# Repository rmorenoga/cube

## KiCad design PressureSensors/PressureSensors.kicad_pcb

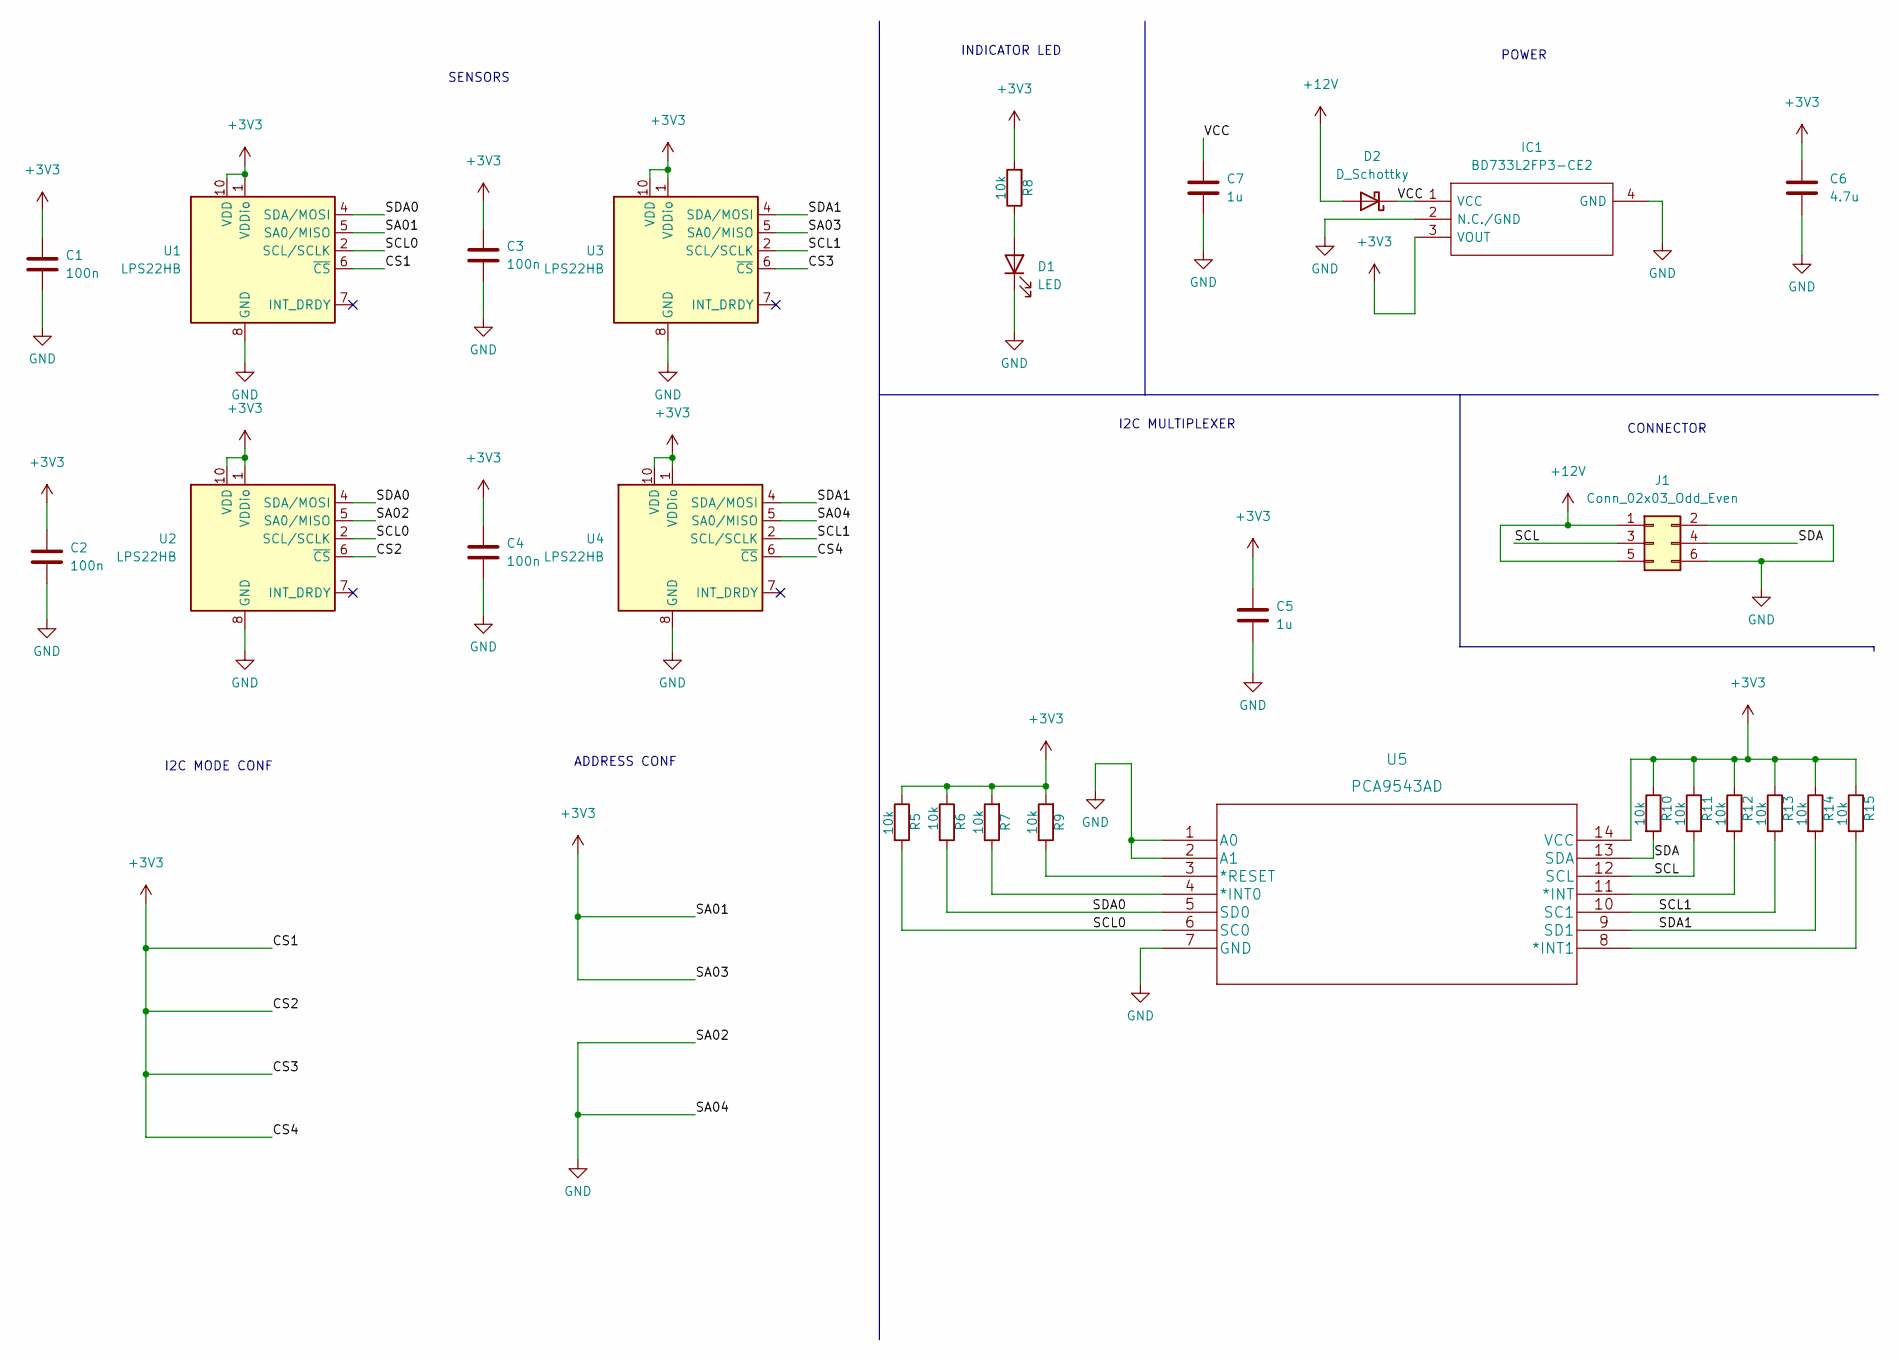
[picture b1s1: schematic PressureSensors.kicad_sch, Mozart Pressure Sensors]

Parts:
C1, C2, C3, C4: 100n; C_0805_2012Metric_Pad1.18x1.45mm_HandSolder
C5, C7: 1u; C_0805_2012Metric_Pad1.18x1.45mm_HandSolder
C6: 4.7u; C_0805_2012Metric_Pad1.18x1.45mm_HandSolder
D1: LED; LED_0805_2012Metric_Pad1.15x1.40mm_HandSolder
D2: D_Schottky; D_SMA
IC1: BD733L2FP3-CE2; SOT230P700X180-4N; Manufacturer_Part_Number BD733L2FP3-CE2
J1: Conn_02x03_Odd_Even; PinHeader_2x03_P2.54mm_Vertical
R5, R6, R7, R8, R9, R10, R11, R12, R13, R14, R15: 10k; R_0805_2012Metric_Pad1.20x1.40mm_HandSolder
U1, U2, U3, U4: LPS22HB; LPS22HBTR
U5: PCA9543AD

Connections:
+3V3: C1.1, C2.1, C3.1, C4.1, C5.1, C6.1, IC1.3 (VOUT), R5.1, R6.1, R7.2, R8.2, R9.2, R10.1, R11.1, R12.1, R13.1, R14.1, R15.1, U1.1 (VDDio), U1.5 (SA0/MISO), U1.6 (~CS), U1.10 (VDD), U2.1 (VDDio), U2.6 (~CS), U2.10 (VDD), U3.1 (VDDio), U3.5 (SA0/MISO), U3.6 (~CS), U3.10 (VDD), U4.1 (VDDio), U4.6 (~CS), U4.10 (VDD), U5.14 (VCC)
+12V: D2.2 (A), J1.1, J1.5
/SCL: J1.3, R11.2, U5.12 (SCL)
/SCL0: R5.2, U1.2 (SCL/SCLK), U2.2 (SCL/SCLK), U5.6 (SC0)
/SCL1: R13.2, U3.2 (SCL/SCLK), U4.2 (SCL/SCLK), U5.10 (SC1)
/SDA: J1.4, R10.2, U5.13 (SDA)
/SDA0: R6.2, U1.4 (SDA/MOSI), U2.4 (SDA/MOSI), U5.5 (SD0)
/SDA1: R14.2, U3.4 (SDA/MOSI), U4.4 (SDA/MOSI), U5.9 (SD1)
/VCC: C7.1, D2.1 (K), IC1.1 (VCC)
GND: C1.2, C2.2, C3.2, C4.2, C5.2, C6.2, C7.2, D1.1 (K), IC1.2 (N.C./GND), IC1.4 (GND), J1.2, J1.6, U1.3 (GND), U1.8 (GND), U1.9 (GND), U2.3 (GND), U2.5 (SA0/MISO), U2.8 (GND), U2.9 (GND), U3.3 (GND), U3.8 (GND), U3.9 (GND), U4.3 (GND), U4.5 (SA0/MISO), U4.8 (GND), U4.9 (GND), U5.1 (A0), U5.2 (A1), U5.7 (GND)
unnamed: D1.2 (A), R8.1
unnamed: R7.1, U5.4 (*INT0)
unnamed: R9.1, U5.3 (*RESET)
unnamed: R12.2, U5.11 (*INT)
unnamed: R15.2, U5.8 (*INT1)

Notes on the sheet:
I2C MODE CONF
CONNECTOR
I2C MULTIPLEXER
INDICATOR LED
SENSORS
POWER
ADDRESS CONF

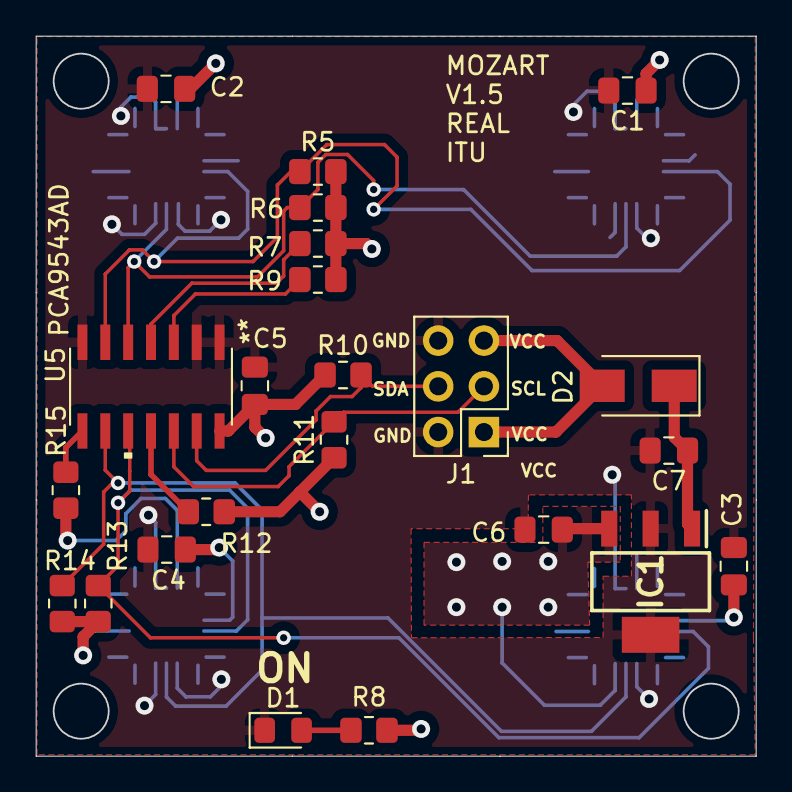
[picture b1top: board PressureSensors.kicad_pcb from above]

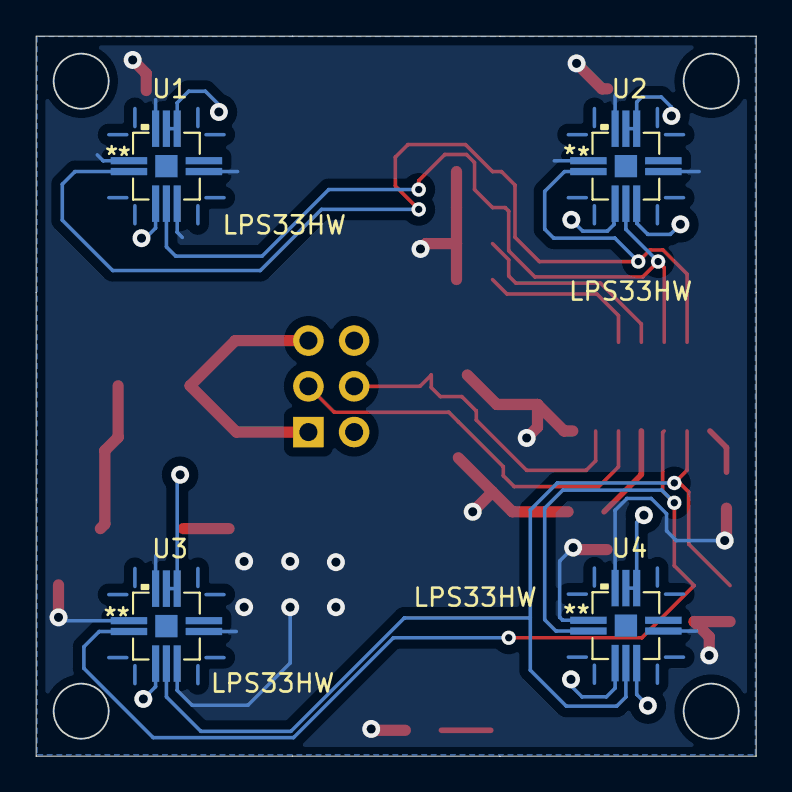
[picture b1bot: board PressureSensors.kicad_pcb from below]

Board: 2 copper layers, 40.0 x 40.0 mm, 27 parts (4 on the bottom side), 15 nets.

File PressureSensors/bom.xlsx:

Source: | C:\Users\rodr\git\cube\PressureSensors\PressureSensors.kicad_sch
Date: | 44909.482256944444
Tool: | Eeschema (6.0.5)
Generator: | C:\Program Files\KiCad\6.0\bin\scripting\plugins/bom_csv_grouped_by_value.py
Component Count: | 27
Individual Components:
Item | Qty | Reference(s) | Value | LibPart | Footprint | Datasheet | Description | Height | Manufacturer_Name | Manufacturer_Part_Number | RS Part Number | RS Price/Stock
 |  | C1 | 100n | Device:C | Capacitor_SMD:C_0805_2012Metric_Pad1.18x1.45mm_HandSolder | ~
 |  | C2 | 100n | Device:C | Capacitor_SMD:C_0805_2012Metric_Pad1.18x1.45mm_HandSolder | ~
 |  | C3 | 100n | Device:C | Capacitor_SMD:C_0805_2012Metric_Pad1.18x1.45mm_HandSolder | ~
 |  | C4 | 100n | Device:C | Capacitor_SMD:C_0805_2012Metric_Pad1.18x1.45mm_HandSolder | ~
 |  | C5 | 1u | Device:C | Capacitor_SMD:C_0805_2012Metric_Pad1.18x1.45mm_HandSolder | ~
 |  | C6 | 4.7u | Device:C | Capacitor_SMD:C_0805_2012Metric_Pad1.18x1.45mm_HandSolder | ~
 |  | C7 | 1u | Device:C | Capacitor_SMD:C_0805_2012Metric_Pad1.18x1.45mm_HandSolder | ~
 |  | D1 | LED | Device:LED | LED_SMD:LED_0805_2012Metric_Pad1.15x1.40mm_HandSolder | ~
 |  | D2 | D_Schottky | Device:D_Schottky | Diode_SMD:D_SMA | ~
 |  | IC1 | BD733L2FP3-CE2 | Custom:BD733L2FP3-CE2 | Custom:SOT230P700X180-4N | http://uk.rs-online.com/web/p/products/1288876P | ROHM BD733L2FP3-CE2, LDO Regulator, 200mA, 3.3 V, +/-2%, 4.37 45 Vin, SOT-223-4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 | 1.8 | ROHM Semiconductor | BD733L2FP3-CE2 | 1288876P | http://uk.rs-online.com/web/p/products/1288876P
 |  | J1 | Conn_02x03_Odd_Even | Connector_Generic:Conn_02x03_Odd_Even | Connector_PinHeader_2.54mm:PinHeader_2x03_P2.54mm_Vertical | ~
 |  | R5 | 10k | Device:R | Resistor_SMD:R_0805_2012Metric_Pad1.20x1.40mm_HandSolder | ~
 |  | R6 | 10k | Device:R | Resistor_SMD:R_0805_2012Metric_Pad1.20x1.40mm_HandSolder | ~
 |  | R7 | 10k | Device:R | Resistor_SMD:R_0805_2012Metric_Pad1.20x1.40mm_HandSolder | ~
 |  | R8 | 10k | Device:R | Resistor_SMD:R_0805_2012Metric_Pad1.20x1.40mm_HandSolder | ~
 |  | R9 | 10k | Device:R | Resistor_SMD:R_0805_2012Metric_Pad1.20x1.40mm_HandSolder | ~
 |  | R10 | 10k | Device:R | Resistor_SMD:R_0805_2012Metric_Pad1.20x1.40mm_HandSolder | ~
 |  | R11 | 10k | Device:R | Resistor_SMD:R_0805_2012Metric_Pad1.20x1.40mm_HandSolder | ~
 |  | R12 | 10k | Device:R | Resistor_SMD:R_0805_2012Metric_Pad1.20x1.40mm_HandSolder | ~
 |  | R13 | 10k | Device:R | Resistor_SMD:R_0805_2012Metric_Pad1.20x1.40mm_HandSolder | ~
 |  | R14 | 10k | Device:R | Resistor_SMD:R_0805_2012Metric_Pad1.20x1.40mm_HandSolder | ~
 |  | R15 | 10k | Device:R | Resistor_SMD:R_0805_2012Metric_Pad1.20x1.40mm_HandSolder | ~
 |  | U1 | LPS22HB | Custom:LPS22HB | Custom:LPS22HBTR | www.st.com/resource/en/datasheet/lps22hb.pdf
 |  | U2 | LPS22HB | Custom:LPS22HB | Custom:LPS22HBTR | www.st.com/resource/en/datasheet/lps22hb.pdf
 |  | U3 | LPS22HB | Custom:LPS22HB | Custom:LPS22HBTR | www.st.com/resource/en/datasheet/lps22hb.pdf
 |  | U4 | LPS22HB | Custom:LPS22HB | Custom:LPS22HBTR | www.st.com/resource/en/datasheet/lps22hb.pdf
 |  | U5 | PCA9543AD | Custom:PCA9543AD | Custom:PCA9543AD
Collated Components:
Item | Qty | Reference(s) | Value | LibPart | Footprint | Datasheet | Description | Height | Manufacturer_Name | Manufacturer_Part_Number | RS Part Number | RS Price/Stock
1 | 4 | C1, C2, C3, C4 | 100n | Device:C | Capacitor_SMD:C_0805_2012Metric_Pad1.18x1.45mm_HandSolder | ~ |  |  |  |  | 264-4416 | In house
2 | 2 | C5, C7 | 1u | Device:C | Capacitor_SMD:C_0805_2012Metric_Pad1.18x1.45mm_HandSolder | ~ |  |  |  |  | 198-8112
3 | 1 | C6 | 4.7u | Device:C | Capacitor_SMD:C_0805_2012Metric_Pad1.18x1.45mm_HandSolder | ~ |  |  |  |  | 172-1502
4 | 1 | D1 | LED | Device:LED | LED_SMD:LED_0805_2012Metric_Pad1.15x1.40mm_HandSolder | ~ |  |  |  |  |  | In house
5 | 1 | D2 | D_Schottky | Device:D_Schottky | Diode_SMD:D_SMA | ~ |  |  |  |  | 688-2246
6 | 1 | IC1 | BD733L2FP3-CE2 | Custom:BD733L2FP3-CE2 | Custom:SOT230P700X180-4N | http://uk.rs-online.com/web/p/products/1288876P | ROHM BD733L2FP3-CE2, LDO Regulator, 200mA, 3.3 V, +/-2%, 4.37 45 Vin, SOT-223-4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 | 1.8 | ROHM Semiconductor | BD733L2FP3-CE2 | 1288876P | http://uk.rs-online.com/web/p/products/1288876P
7 | 1 | J1 | Conn_02x03_Odd_Even | Connector_Generic:Conn_02x03_Odd_Even | Connector_PinHeader_2.54mm:PinHeader_2x03_P2.54mm_Vertical | ~ |  |  |  |  |  | In house
8 | 11 | R5, R6, R7, R8, R9, R10, R11, R12, R13, R14, R15 | 10k | Device:R | Resistor_SMD:R_0805_2012Metric_Pad1.20x1.40mm_HandSolder | ~ |  |  |  |  |  | In house
9 | 4 | U1, U2, U3, U4 | LPS22HB | Custom:LPS22HB | Custom:LPS22HBTR | www.st.com/resource/en/datasheet/lps22hb.pdf |  |  |  |  |  | https://www.digikey.dk/da/products/detail/stmicroelectronics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
10 | 1 | U5 | PCA9543AD | Custom:PCA9543AD | Custom:PCA9543AD |  |  |  |  |  |  | https://www.digikey.dk/da/products/detail/texas-instruments/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

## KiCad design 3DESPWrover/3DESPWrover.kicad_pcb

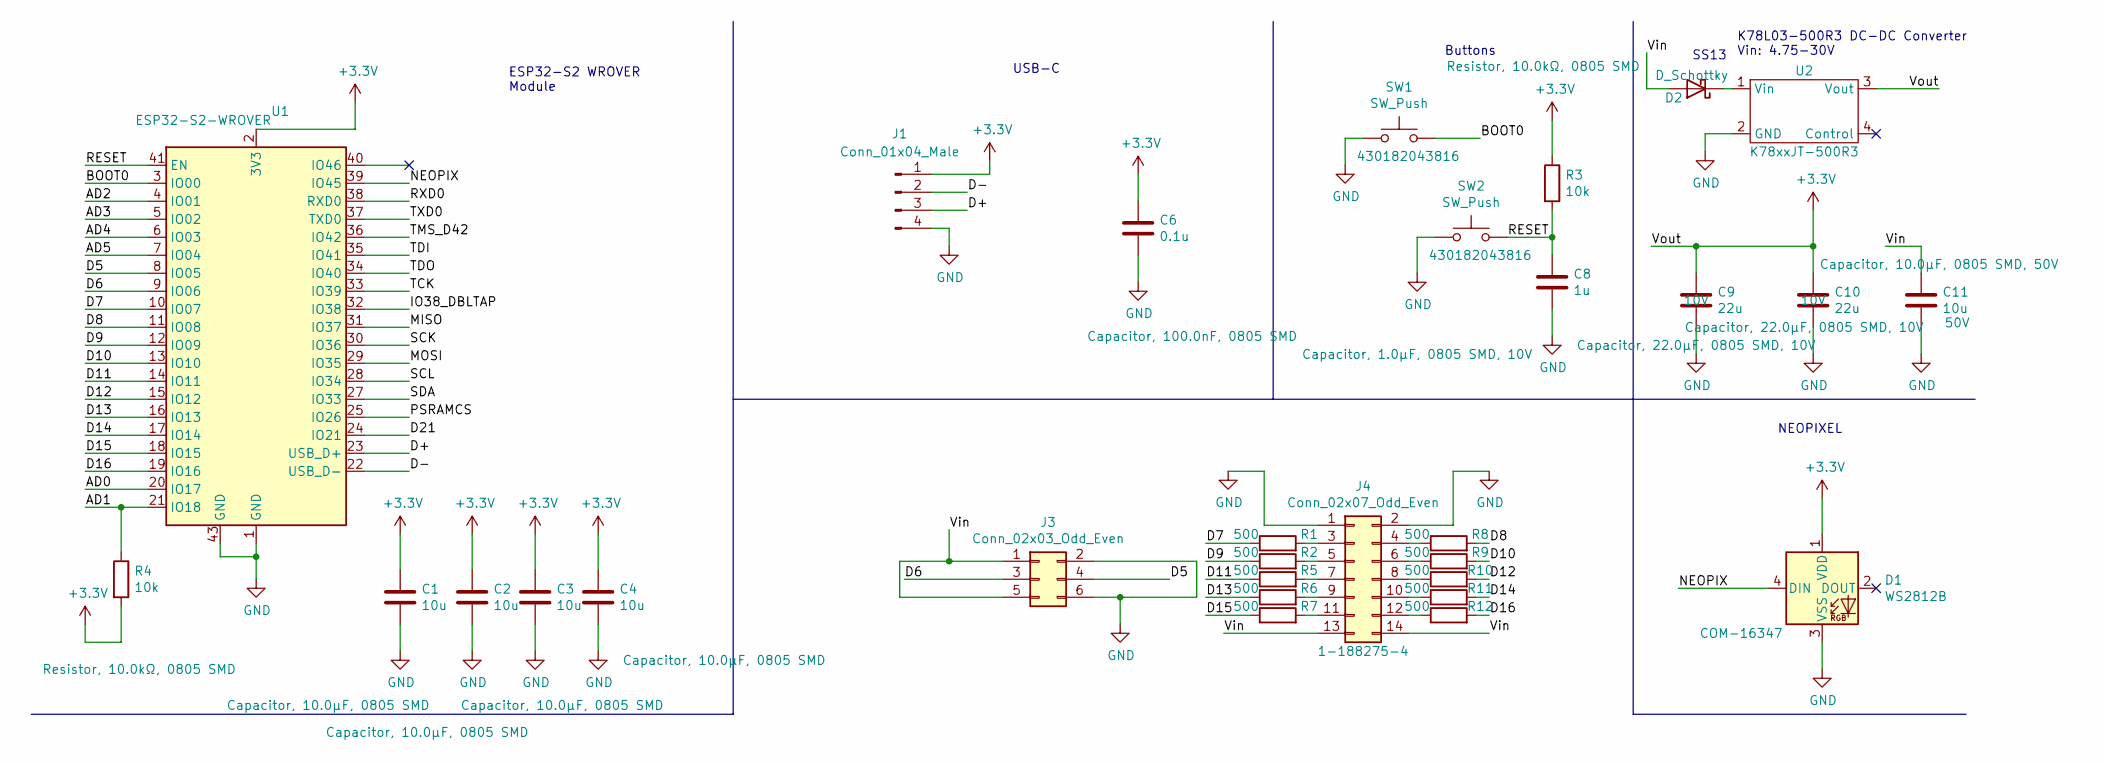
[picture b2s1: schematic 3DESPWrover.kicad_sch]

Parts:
C1, C2, C3, C4: 10u; C_0805_2012Metric_Pad1.18x1.45mm_HandSolder; MPN Capacitor, 10.0µF, 0805 SMD
C6: 0.1u; C_0805_2012Metric_Pad1.18x1.45mm_HandSolder; MPN Capacitor, 100.0nF, 0805 SMD
C8: 1u; C_0805_2012Metric_Pad1.18x1.45mm_HandSolder; MPN Capacitor, 1.0µF, 0805 SMD, 10V
C9, C10: 22u; C_0805_2012Metric_Pad1.18x1.45mm_HandSolder; Voltage 10V; MPN Capacitor, 22.0µF, 0805 SMD, 10V
C11: 10u; C_0805_2012Metric_Pad1.18x1.45mm_HandSolder; Voltage 50V; MPN Capacitor, 10.0µF, 0805 SMD, 50V
D1: WS2812B; LED_WS2812B_PLCC4_5.0x5.0mm_P3.2mm; MPN COM-16347
D2: D_Schottky; D_SMA; MPN SS13
J1: Conn_01x04_Male; PinHeader_1x04_P2.54mm_Vertical; MPN 0022052041
J3: Conn_02x03_Odd_Even; PinHeader_2x03_P2.54mm_Vertical; MPN SSW-103-01-F-D
J4: Conn_02x07_Odd_Even; TE_Micromatch_2,54_14_SMD; MPN 1-188275-4
R1, R2, R5, R6, R7, R8, R9, R10, R11, R12: 500; R_0603_1608Metric_Pad0.98x0.95mm_HandSolder; MPN Resistor, 510.0Ω, 0603 SMD
R3, R4: 10k; R_0805_2012Metric_Pad1.20x1.40mm_HandSolder; MPN Resistor, 10.0kΩ, 0805 SMD
SW1, SW2: SW_Push; SW_SPST_B3S-1000; MPN 430182043816
U1: ESP32-S2-WROVER; MPN DFR0743-WROVER
U2: K78xxJT-500R3; K7803JT-500R3-SMD; MPN K7803JT-500R3

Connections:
+3V3: C1.1, C2.1, C3.1, C4.1, C6.1, C9.1, C10.1, D1.1 (VDD), J1.1, R3.1, R4.2, U1.2 (3V3), U2.3 (Vout)
/AD0: U1.20 (IO17)
/AD1: R4.1, U1.21 (IO18)
/AD2: U1.4 (IO01)
/AD3: U1.5 (IO02)
/AD4: U1.6 (IO03)
/AD5: U1.7 (IO04)
/BOOT0: SW1.2, U1.3 (IO00)
/D5: J3.4, U1.8 (IO05)
/D6: J3.3, U1.9 (IO06)
/D7: R1.1, U1.10 (IO07)
/D8: R8.2, U1.11 (IO08)
/D9: R2.1, U1.12 (IO09)
/D10: R9.2, U1.13 (IO10)
/D11: R5.1, U1.14 (IO11)
/D12: R10.2, U1.15 (IO12)
/D13: R6.1, U1.16 (IO13)
/D14: R11.2, U1.17 (IO14)
/D15: R7.1, U1.18 (IO15)
/D16: R12.2, U1.19 (IO16)
/D21: U1.24 (IO21)
/D+: J1.3, U1.23 (USB_D+)
/D-: J1.2, U1.22 (USB_D-)
/IO38_DBLTAP: U1.32 (IO38)
/MISO: U1.31 (IO37)
/MOSI: U1.29 (IO35)
/NEOPIX: D1.4 (DIN), U1.39 (IO45)
/PSRAMCS: U1.25 (IO26)
/RESET: C8.1, R3.2, SW2.2, U1.41 (EN)
/RXD0: U1.38 (RXD0)
/SCK: U1.30 (IO36)
/SCL: U1.28 (IO34)
/SDA: U1.27 (IO33)
/TCK: U1.33 (IO39)
/TDI: U1.35 (IO41)
/TDO: U1.34 (IO40)
/TMS_D42: U1.36 (IO42)
/TXD0: U1.37 (TXD0)
/Vin: C11.1, D2.2 (A), J3.1, J3.5, J4.13, J4.14
GND: C1.2, C2.2, C3.2, C4.2, C6.2, C8.2, C9.2, C10.2, C11.2, D1.3 (VSS), J1.4, J3.2, J3.6, J4.1, J4.2, SW1.1, SW2.1, U1.1 (GND), U1.26 (GND), U1.42 (GND), U1.43 (GND), U1.44 (GND), U1.45 (GND), U1.46 (GND), U1.47 (GND), U1.48 (GND), U1.49 (GND), U1.50 (GND), U1.51 (GND), U2.2 (GND)
unnamed: D2.1 (K), U2.1 (Vin)
unnamed: J4.3, R1.2
unnamed: J4.4, R8.1
unnamed: J4.5, R2.2
unnamed: J4.6, R9.1
unnamed: J4.7, R5.2
unnamed: J4.8, R10.1
unnamed: J4.9, R6.2
unnamed: J4.10, R11.1
unnamed: J4.11, R7.2
unnamed: J4.12, R12.1

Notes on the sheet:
Buttons
K78L03-500R3 DC-DC Converter Vin: 4.75-30V
NEOPIXEL
ESP32-S2 WROVER Module
USB-C
SS13

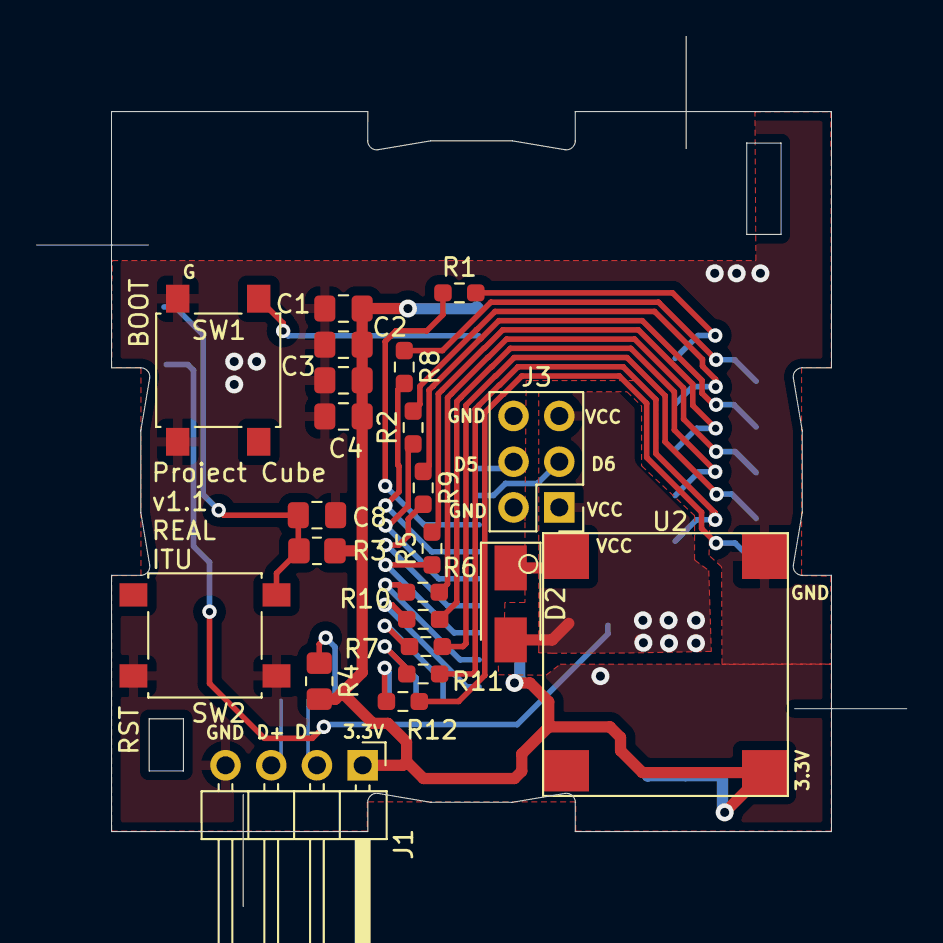
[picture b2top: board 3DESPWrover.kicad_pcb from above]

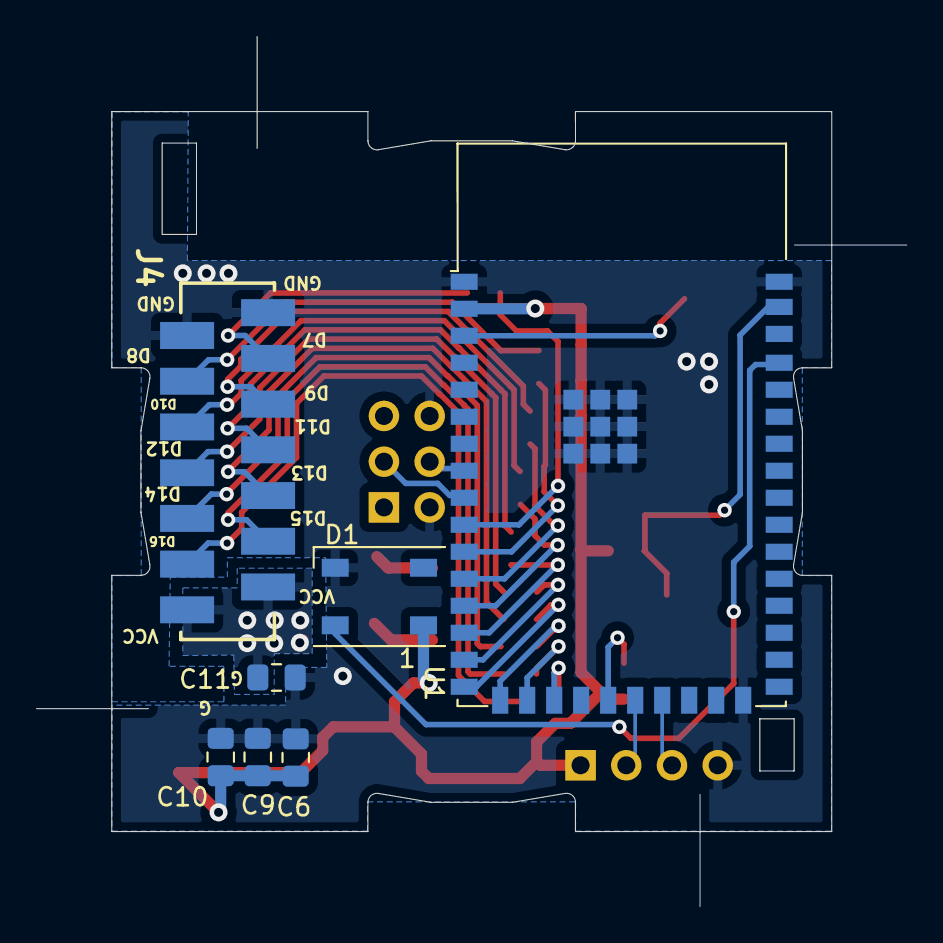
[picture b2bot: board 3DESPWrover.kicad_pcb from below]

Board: 2 copper layers, 40.0 x 40.0 mm, 30 parts (7 on the bottom side), 32 nets.

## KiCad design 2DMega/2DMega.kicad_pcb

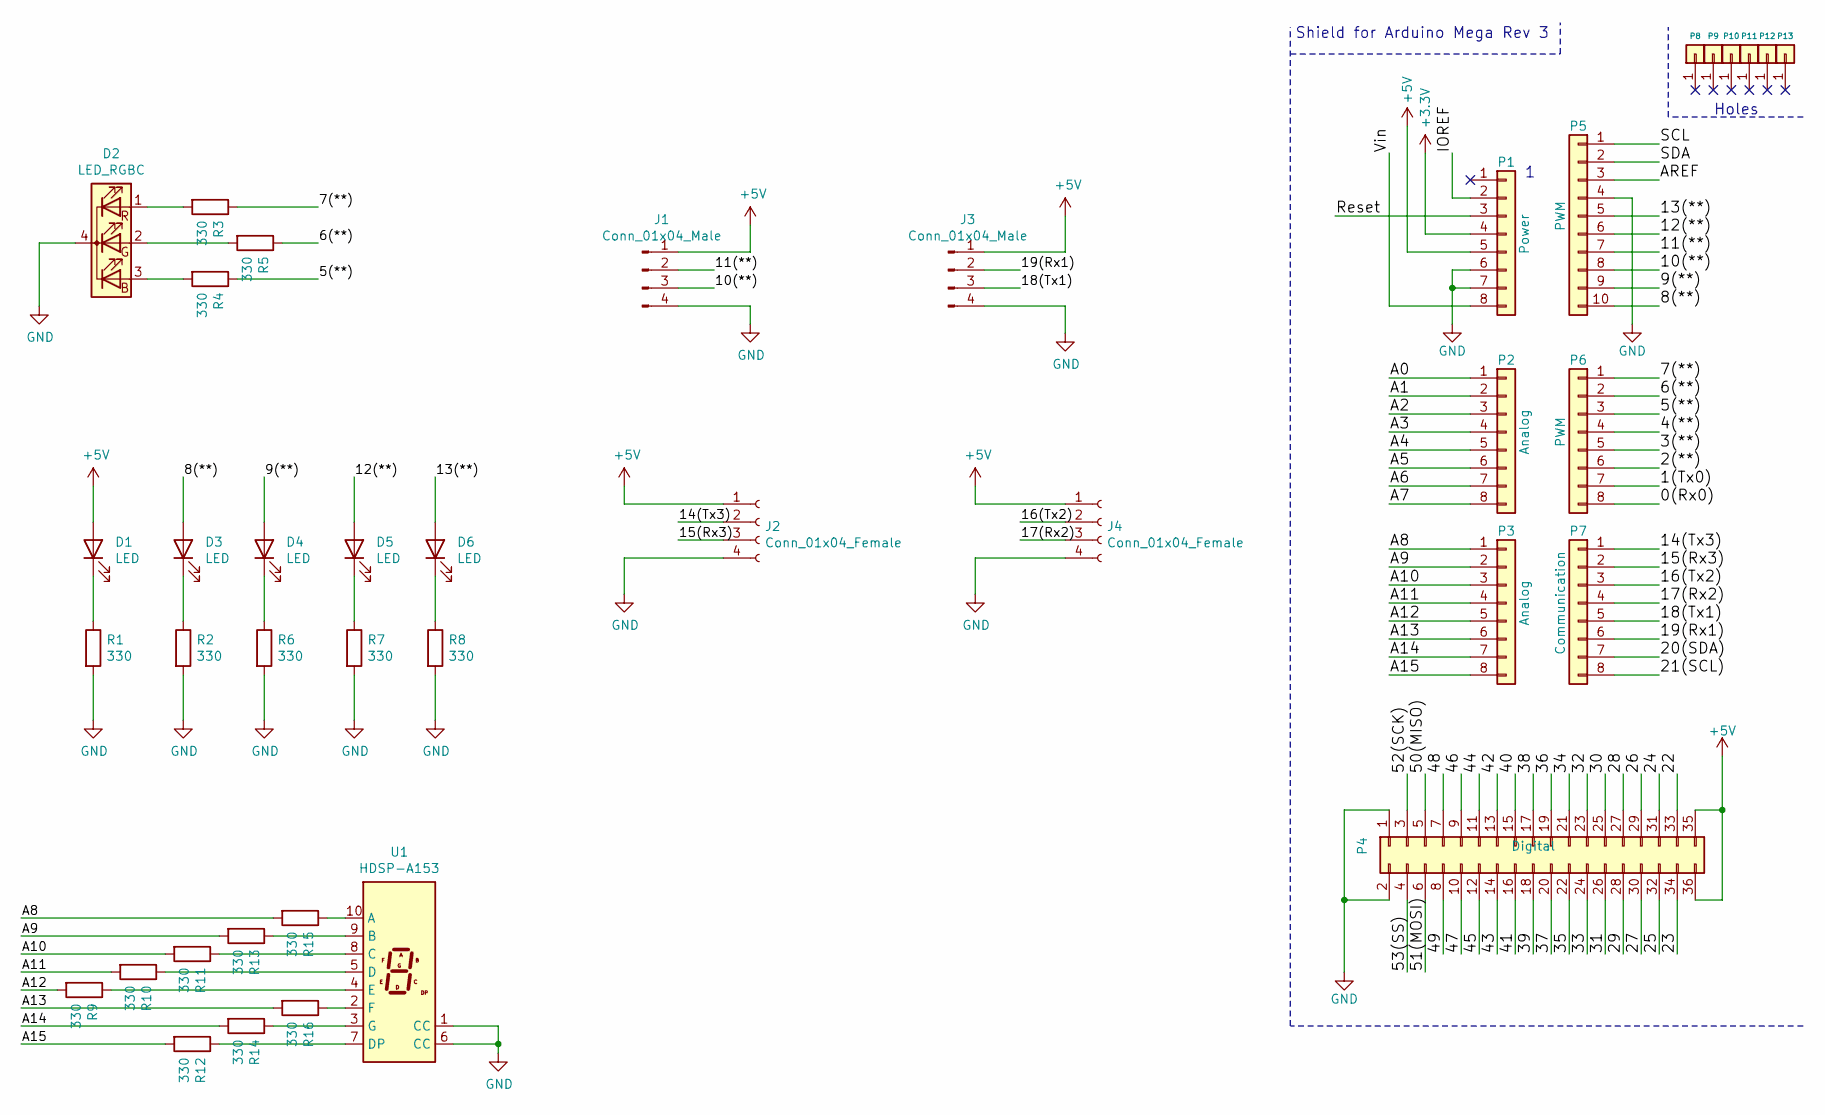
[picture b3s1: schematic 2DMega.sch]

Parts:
D1, D3, D4, D5, D6: LED; LED_D5.0mm
D2: LED_RGBC; LED_D5.0mm-4_RGB
J1, J3: Conn_01x04_Male; PinHeader_1x04_P2.54mm_Horizontal
J2, J4: Conn_01x04_Female; PinSocket_1x04_P2.54mm_Horizontal
P1: Power; Socket_Strip_Arduino_2x18
P2, P3: Analog; Socket_Strip_Arduino_1x08
P4: Digital; Socket_Strip_Arduino_1x08
P5: PWM; Socket_Strip_Arduino_1x10
P6: PWM; Socket_Strip_Arduino_1x08
P7: Communication; Socket_Strip_Arduino_1x08
P8, P9, P10, P11, P12, P13: CONN_01X01; Arduino_1pin
R1, R2, R3, R4, R5, R6, R7, R8, R9, R10, R11, R12, R13, R14, R15, R16: 330; R_Axial_DIN0207_L6.3mm_D2.5mm_P10.16mm_Horizontal
U1: HDSP-A153; HDSP-A151

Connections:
+3V3: P1.4
+5V: D1.2 (A), J1.1, J2.1, J3.1, J4.1, P1.5, P4.35, P4.36
/0(Rx0): P6.8
/1(Tx0): P6.7
/2(**): P6.6
/3(**): P6.5
/4(**): P6.4
/5(**): P6.3, R4.1
/6(**): P6.2, R5.1
/7(**): P6.1, R3.1
/8(**): D3.2 (A), P5.10
/9(**): D4.2 (A), P5.9
/10(**): J1.3, P5.8
/11(**): J1.2, P5.7
/12(**): D5.2 (A), P5.6
/13(**): D6.2 (A), P5.5
/14(Tx3): J2.2, P7.1
/15(Rx3): J2.3, P7.2
/16(Tx2): J4.2, P7.3
/17(Rx2): J4.3, P7.4
/18(Tx1): J3.3, P7.5
/19(Rx1): J3.2, P7.6
/20(SDA): P7.7
/21(SCL): P7.8
/22: P4.33
/23: P4.34
/24: P4.31
/25: P4.32
/26: P4.29
/27: P4.30
/28: P4.27
/29: P4.28
/30: P4.25
/31: P4.26
/32: P4.23
/33: P4.24
/34: P4.21
/35: P4.22
/36: P4.19
/37: P4.20
/38: P4.17
/39: P4.18
/40: P4.15
/41: P4.16
/42: P4.13
/43: P4.14
/44: P4.11
/45: P4.12
/46: P4.9
/47: P4.10
/48: P4.7
/49: P4.8
/50(MISO): P4.5
/51(MOSI): P4.6
/52(SCK): P4.3
/53(SS): P4.4
/A0: P2.1
/A1: P2.2
/A2: P2.3
/A3: P2.4
/A4: P2.5
/A5: P2.6
/A6: P2.7
/A7: P2.8
/A8: P3.1, R15.2
/A9: P3.2, R13.2
/A10: P3.3, R11.2
/A11: P3.4, R10.2
/A12: P3.5, R9.2
/A13: P3.6, R16.2
/A14: P3.7, R14.2
/A15: P3.8, R12.2
/AREF: P5.3
/IOREF: P1.2
/Reset: P1.3
/SCL: P5.1
/SDA: P5.2
/Vin: P1.8
GND: D2.4 (K), J1.4, J2.4, J3.4, J4.4, P1.6, P1.7, P4.1, P4.2, P5.4, R1.2, R2.2, R6.2, R7.2, R8.2, U1.1 (CC), U1.6 (CC)
unnamed: D1.1 (K), R1.1
unnamed: D2.1 (RA), R3.2
unnamed: D2.2 (GA), R5.2
unnamed: D2.3 (BA), R4.2
unnamed: D3.1 (K), R2.1
unnamed: D4.1 (K), R6.1
unnamed: D5.1 (K), R7.1
unnamed: D6.1 (K), R8.1
unnamed: R9.1, U1.4 (E)
unnamed: R10.1, U1.5 (D)
unnamed: R11.1, U1.8 (C)
unnamed: R12.1, U1.7 (DP)
unnamed: R13.1, U1.9 (B)
unnamed: R14.1, U1.3 (G)
unnamed: R15.1, U1.10 (A)
unnamed: R16.1, U1.2 (F)

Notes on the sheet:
Shield for Arduino Mega Rev 3
Holes

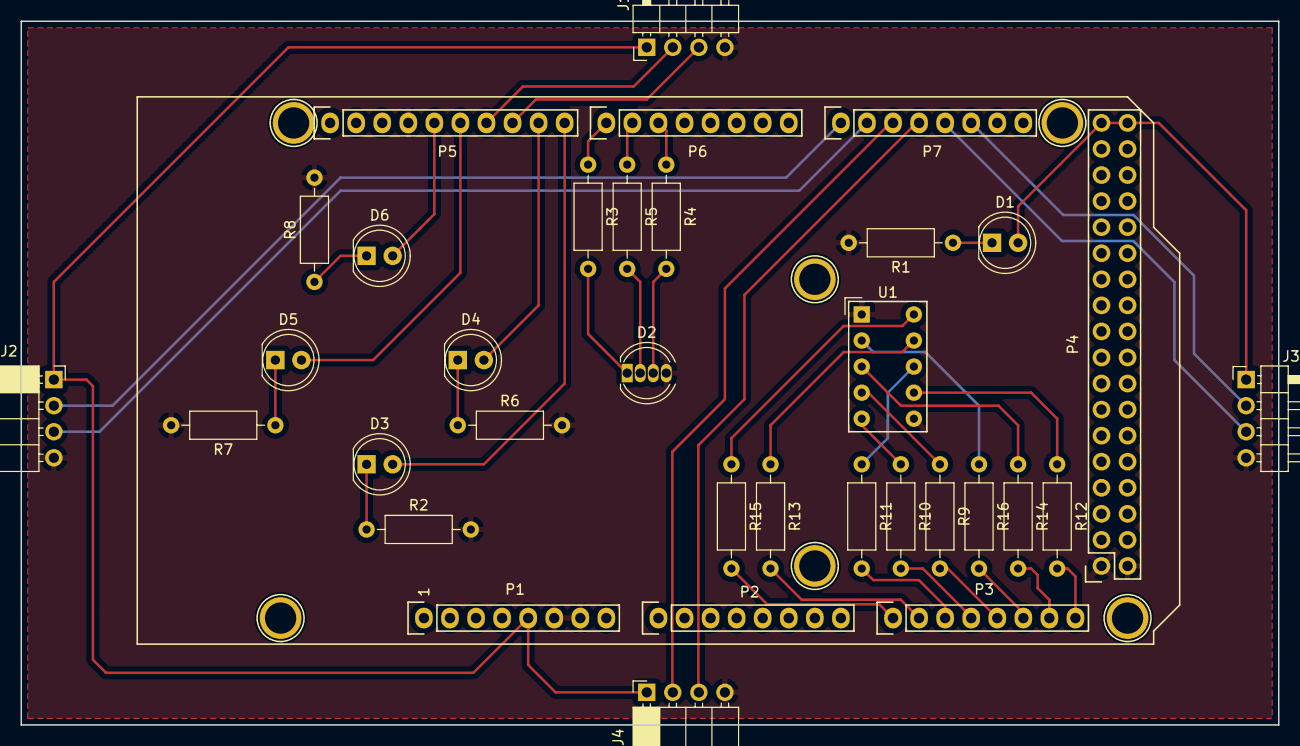
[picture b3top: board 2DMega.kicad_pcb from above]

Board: 2 copper layers, 122.6 x 68.6 mm, 40 parts (0 on the bottom side), 41 nets.

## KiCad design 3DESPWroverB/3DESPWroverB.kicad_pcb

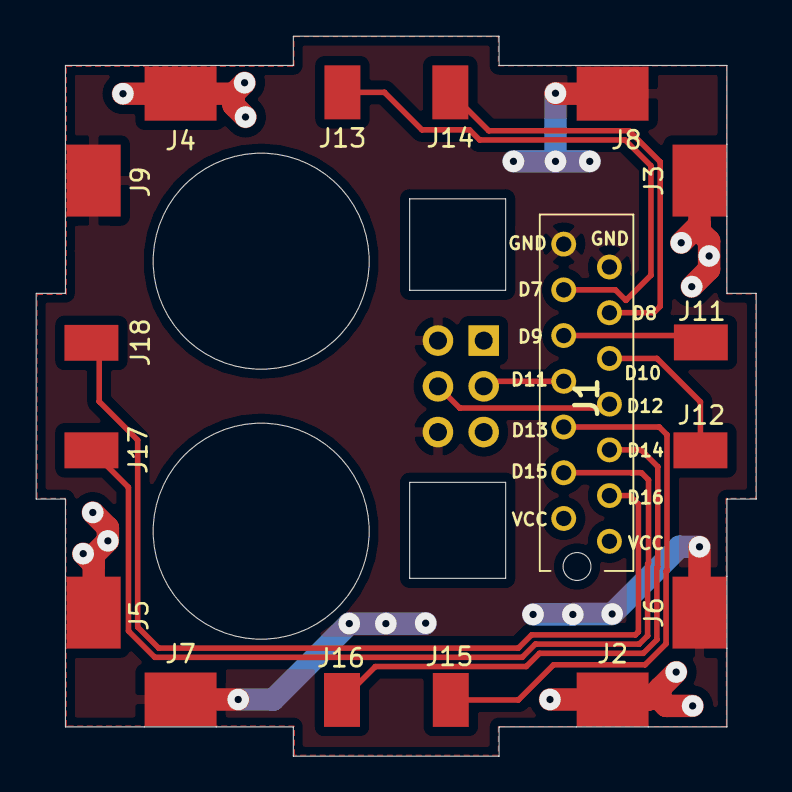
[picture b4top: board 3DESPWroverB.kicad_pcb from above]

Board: 2 copper layers, 40.0 x 40.0 mm, 18 parts (1 on the bottom side), 12 nets.

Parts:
J1: Conn_02x07_Odd_Even; TE_Micromatch_2,54_14
J2, J3, J4, J5, J6, J7, J8, J9: Conn_01x01; CubeSidePad
J10: Conn_02x03_Odd_Even; PinHeader_2x03_P2.54mm_Vertical
J11, J12, J13, J14, J15, J16, J17, J18: Conn_01x01; CubeCenterPad

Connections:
/D7: J1.3, J13.1
/D8: J1.4, J14.1
/D9: J1.5, J11.1
/D10: J1.6, J12.1
/D11: J1.7, J10.3
/D12: J1.8, J10.4
/D13: J1.9, J15.1
/D14: J1.10, J16.1
/D15: J1.11, J17.1
/D16: J1.12, J18.1
GND: J1.1, J1.2, J6.1, J7.1, J8.1, J9.1, J10.2, J10.6
VCC: J1.13, J1.14, J2.1, J3.1, J4.1, J5.1, J10.1, J10.5

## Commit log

2021-08-16 Changed to square
2021-08-17 Added RGB_LED, reorganized pins
2021-08-20 Added button and BOM
2021-08-24 Added resistors to tx and rx pins, silkscreen tags
2021-09-07 As built
2021-09-10 Created basic blink test for the board
2021-12-16 Added 3DESPWrover kicad board
2021-12-22 Cleared Andres comments
2021-12-23 Added 3DESPWroverBottom
2021-12-23 Added 3DESPWroverSideBoard
2021-12-26 Made corrections and added holes for zipties/nylon
2022-01-02 Generated Gerber files for 3D
2022-01-13 Changes to holes
2022-05-16 Correction to 3.3v regulator connection
2022-05-16 Replaced TE connector and regulator to smd on top board
2022-05-20 Some components replaced by SMD versions
2022-06-08 Corrected switching step down power source connections and added mill corner paths
2022-06-17 Ordered
2022-08-23 Python scripts to programatically upload firmware OTA to ESP32s
2022-08-23 Modified OTA function to sweep an ip range
2022-11-22 Added 0805 diode before 3.3 power source
2022-12-05 Updated esp32 footprint for 9 ground path underneath and correcting misalignments
    Added protection resistors to digital pins
    Moved decoupling capacitors closer to 3.3v line
    Corrected legend positions and added indication of boot and reset buttons
2022-12-05 Designed Pressure sensors PCB
2022-12-05 Tidying up design sheets
2022-12-12 Changed I2C multiplexer to 2 channel
    Changed power source to LDO
    Corrected spacing between sensors
    Added missing capacitor for sensors
    Eliminated unnecesary resistors for sensors
2022-12-12 Routed with new components
    Deleted address selection resistors
2022-12-13 DRC check for v1.1 of pressure sensors board
2022-12-13 Flipped side of sensor capacitors
2022-12-13 Changed power source capacitor from 0.1u to 1u
2022-12-13 Sent PressureSensors PCB to manufacturing
2022-12-14 Reduced solder paste area in central ground pads of ESP32
2023-01-04 Sent cube to assembly manufacture, soldered PressureSensors, created test sketch for pressure sensors for arduino uno
2023-02-15 Sent sides to manufacture
2023-02-27 Added basic board test for LED in 3D board
2023-03-03 Pressure sensor weight test, OTAupload debug for ESP32
2025-04-11 Before PC swap

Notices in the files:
parts and their libraries:
Copyright 2021 Accelerated Designs. All rights reserved.
